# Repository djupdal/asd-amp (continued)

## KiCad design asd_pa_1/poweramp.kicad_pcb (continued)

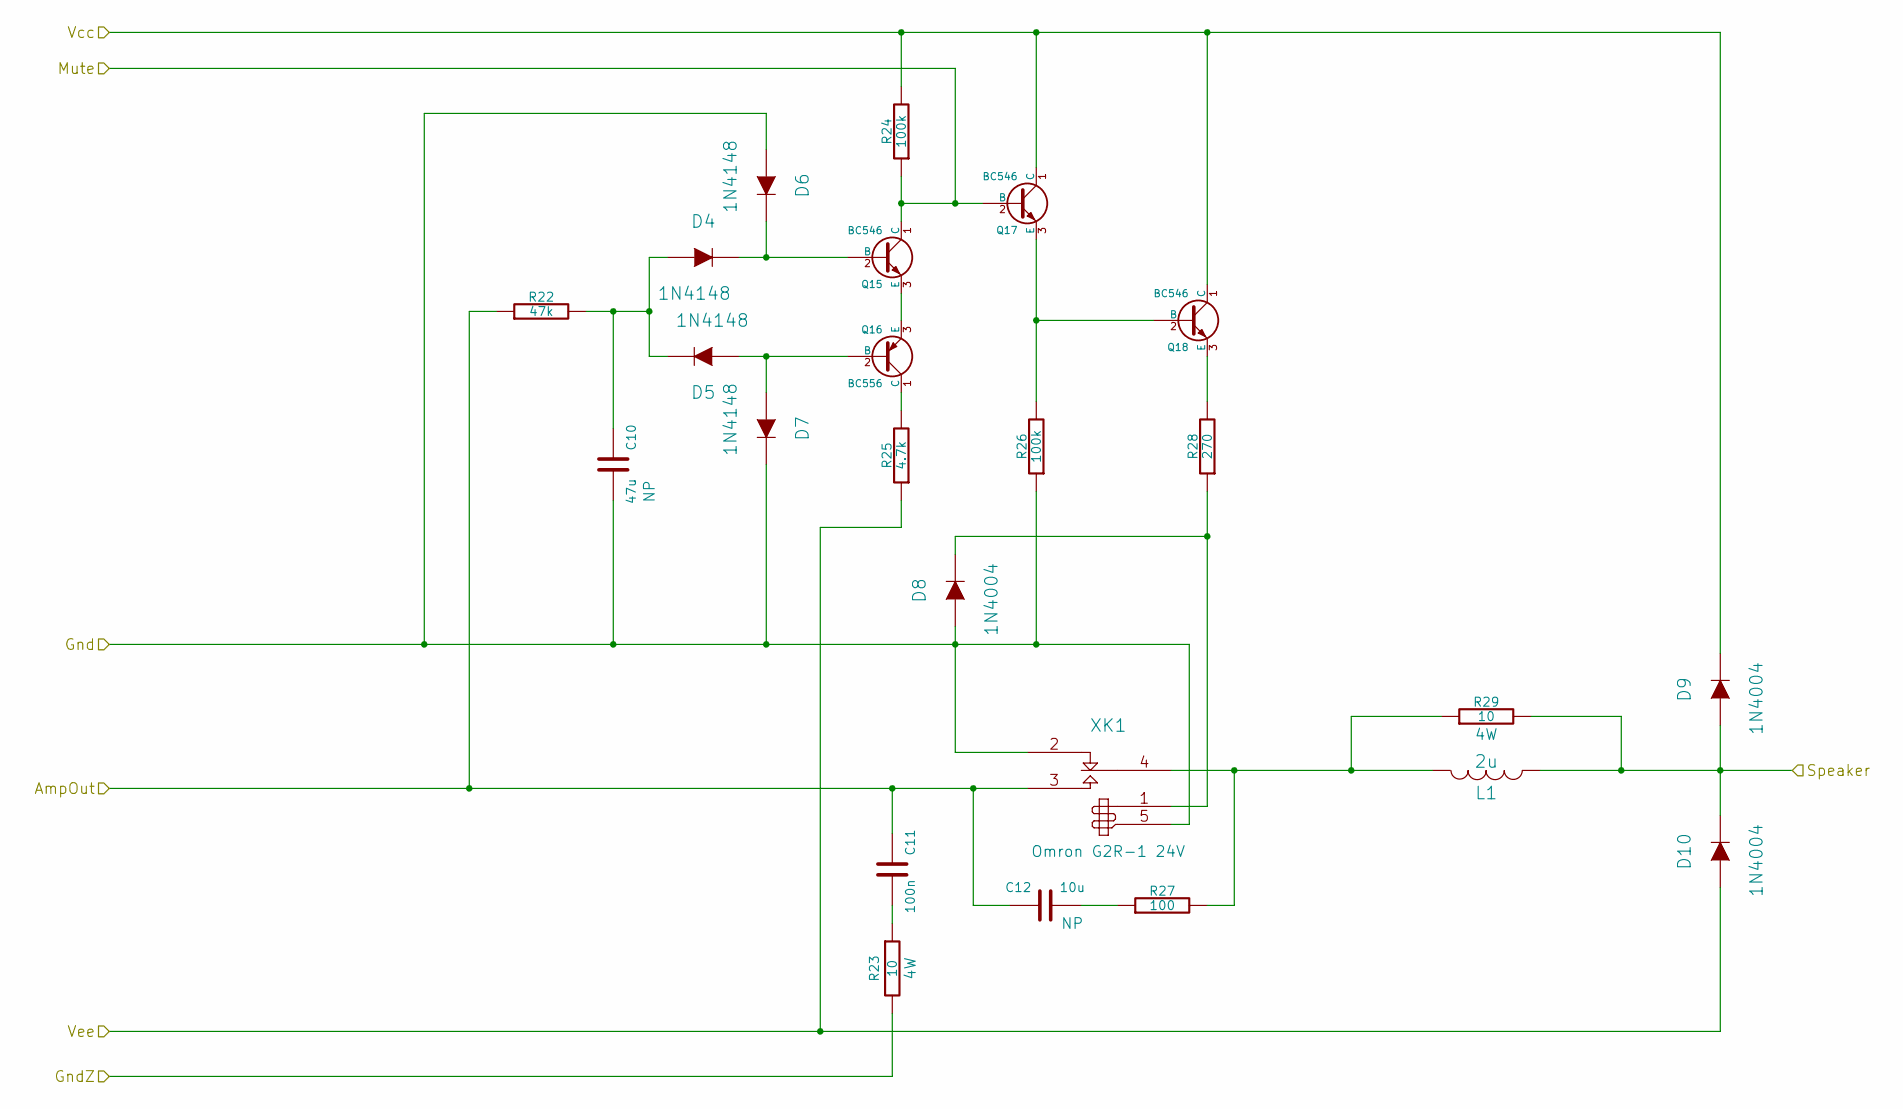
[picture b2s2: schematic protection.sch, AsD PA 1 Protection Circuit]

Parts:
C10: 47u; 47u_NP
C11: 100n; Capacitor7x2.5RM5
C12: 10u; 47u_NP
D4, D5, D6, D7: 1N4148; Diode_DO-35_SOD27_Horizontal_RM10
D8, D9, D10: 1N4004; Diode_DO-41_SOD81_Horizontal_RM10
L1: 2u; Inductor_AirCore_2uH
Q15, Q17, Q18: BC546; TO-92-Free-inline-narrow-oval
Q16: BC556; TO-92-Free-inline-narrow-oval
R22: 47k; Resistor_Horizontal_RM10mm
R23, R29: 10; Resistor_Horizontal_RM15mm
R24, R26: 100k; Resistor_Horizontal_RM10mm
R25: 4.7k; Resistor_Horizontal_RM10mm
R27: 100; Resistor_Horizontal_RM10mm
R28: 270; Resistor_Horizontal_RM10mm
XK1: RELAY_SPDT; Omron_G2R_SPDT

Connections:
/Protection/AmpOut: C11.1, C12.1, R22.1, XK1.3 (T1); also elsewhere on the board
/Protection/Gnd: C10.2, D6.1 (A), D7.2 (K), D8.1 (A), R26.1, XK1.2 (R1), XK1.5; also elsewhere on the board
/Protection/GndZ: R23.2; also elsewhere on the board
/Protection/Mute: Q15.1 (C), Q17.2 (B), R24.1; also elsewhere on the board
/Protection/Speaker: D9.1 (A), D10.2 (K), L1.2, R29.2; also elsewhere on the board
unnamed: C10.1, D4.1 (A), D5.2 (K), R22.2
unnamed: C11.2, R23.1
unnamed: C12.2, R27.1
unnamed: D4.2 (K), D6.2 (K), Q15.2 (B)
unnamed: D5.1 (A), D7.1 (A), Q16.2 (B)
unnamed: D8.2 (K), R28.1, XK1.1
unnamed: L1.1, R27.2, R29.1, XK1.4 (C1)
unnamed: Q15.3 (E), Q16.3 (E)
unnamed: Q16.1 (C), R25.2
unnamed: Q17.3 (E), Q18.2 (B), R26.2
unnamed: Q18.3 (E), R28.2
VCC: D9.2 (K), Q17.1 (C), Q18.1 (C), R24.2; also elsewhere on the board
VEE: D10.1 (A), R25.1; also elsewhere on the board

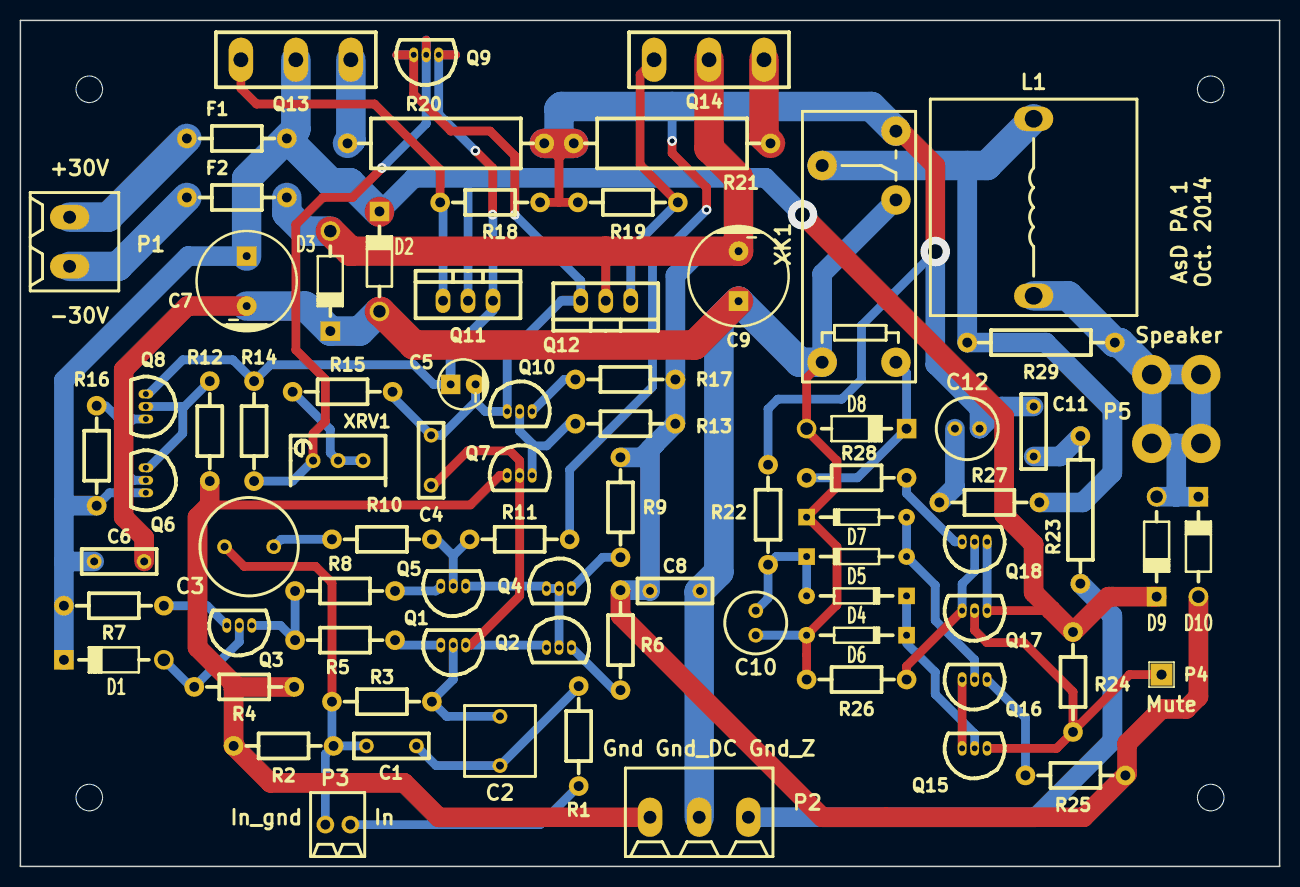
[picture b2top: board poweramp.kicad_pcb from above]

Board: 2 copper layers, 128.0 x 86.0 mm, 83 parts (0 on the bottom side), 48 nets.

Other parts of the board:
MH: MountingHole_2-7mm_RevA_Date21Jun2010; MountingHole_2-7mm
MH#2, MH#3, MH#4: MountingHole_2-7mm_RevA_Date21Jun2010; MountingHole_2-7mm

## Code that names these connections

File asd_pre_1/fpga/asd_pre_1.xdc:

###############################################################################
# Timing constraints
###############################################################################

create_clock -period 20.000 -name mcu_clk [get_ports MCU_OSC]
create_clock -period 88.000 -name audio_clk [get_ports AUDIO_OSC]
create_clock -period 41.000 -name spi_clk [get_ports SCLK]
create_clock -period 40.000 -name spdif_sck [get_ports SCKI1]
create_clock -period 162.000 -name spdif_bck [get_ports BCKI1]
create_clock -period 162.000 -name adc_bck [get_ports BCKI2]

###############################################################################
# Clock groups
###############################################################################

set_clock_groups -asynchronous -group mcu_clk -group audio_clk -group spi_clk -group spdif_sck -group spdif_bck -group adc_bck

###############################################################################
# IO standard
###############################################################################

set_property IOSTANDARD LVCMOS33 [get_ports *]
set_property CFGBVS VCCO [current_design]
set_property CONFIG_VOLTAGE 3.3 [current_design]

###############################################################################
# Location constraints
###############################################################################

# MCU SPI
#set_property PACKAGE_PIN K13 [get_ports INT]
#set_property PACKAGE_PIN P16 [get_ports nSS]
set_property PACKAGE_PIN P16 [get_ports INT]
set_property PACKAGE_PIN K13 [get_ports nSS]
set_property PACKAGE_PIN L14 [get_ports MOSI]
set_property PACKAGE_PIN M16 [get_ports MISO]
set_property PACKAGE_PIN N13 [get_ports SCLK]

# Oscillators
set_property PACKAGE_PIN N14 [get_ports MCU_OSC]
set_property PACKAGE_PIN N11 [get_ports AUDIO_OSC]

# SPDIF routing
set_property PACKAGE_PIN T8 [get_ports SPDIF]
set_property PACKAGE_PIN T9 [get_ports SPDIF_COAX]
set_property PACKAGE_PIN T10 [get_ports SPDIF_TOSLINK]

# SPDIF input
set_property PACKAGE_PIN T7 [get_ports EMPH]
set_property PACKAGE_PIN H13 [get_ports ERROR]
set_property PACKAGE_PIN D13 [get_ports SCKI1]
set_property PACKAGE_PIN H11 [get_ports LRCKI1]
set_property PACKAGE_PIN E11 [get_ports BCKI1]
set_property PACKAGE_PIN H12 [get_ports DIN1]

# ADC input
set_property PACKAGE_PIN B16 [get_ports nOVFL]
set_property PACKAGE_PIN A14 [get_ports SCKO2]
set_property PACKAGE_PIN A13 [get_ports LRCKI2]
set_property PACKAGE_PIN E12 [get_ports BCKI2]
set_property PACKAGE_PIN C14 [get_ports DIN2]

# DAC output
set_property PACKAGE_PIN B11 [get_ports SCKO]
set_property PACKAGE_PIN A10 [get_ports LRCKO]
set_property PACKAGE_PIN A9 [get_ports BCKO]
set_property PACKAGE_PIN A8 [get_ports DOUT]

###############################################################################
# Bitfile constraints
###############################################################################

set_property BITSTREAM.CONFIG.SPI_BUSWIDTH 4 [current_design]
set_property CONFIG_MODE SPIx4 [current_design]

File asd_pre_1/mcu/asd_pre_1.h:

#ifndef ASD_PRE_1_H
#define ASD_PRE_1_H

#define IN_ADDR_T_DEFINED

#include <stdint.h>
#include <stdbool.h>
#include <stddef.h>

#include "efm32gg232f1024.h"

#include "config.h"

#include "em_device.h"
#include "em_cmu.h"
#include "em_gpio.h"
#include "em_i2c.h"
#include "em_system.h"
#include "em_chip.h"
 
#define LED_ON  0
#define LED_OFF 1

#define DAC_ADDRESS 0x98

//

#define LED0_BIT 3
#define LED0_PORT gpioPortF
#define LED1_BIT 4
#define LED1_PORT gpioPortF
#define LED2_BIT GPIO_1_BIT
#define LED2_PORT GPIO_1_PORT
 
#define PROGRAM_B_BIT 4
#define PROGRAM_B_PORT gpioPortA
#define DONE_BIT 5
#define DONE_PORT gpioPortA
#define FPGA_USART USART2
#define FPGA_USART_CLK cmuClock_USART2
#define FPGA_USART_LOC USART_ROUTE_LOCATION_LOC0
#define FPGA_TX_BIT 2
#define FPGA_TX_PORT gpioPortC
#define FPGA_RX_BIT 3
#define FPGA_RX_PORT gpioPortC
#define FPGA_CLK_BIT 4
#define FPGA_CLK_PORT gpioPortC
//#define FPGA_CS_BIT 5
//#define FPGA_CS_PORT gpioPortC
//#define INT_FPGA_BIT 3
//#define INT_FPGA_PORT gpioPortA
#define FPGA_CS_BIT 3
#define FPGA_CS_PORT gpioPortA
#define INT_FPGA_BIT 5
#define INT_FPGA_PORT gpioPortC

#define nRST_SPDIF_BIT 8
#define nRST_SPDIF_PORT gpioPortB

#define nRST_DAC_BIT 15
#define nRST_DAC_PORT gpioPortE

#define nRST_ADC_BIT 14
#define nRST_ADC_PORT gpioPortE
#define nHPF_BIT 13
#define nHPF_PORT gpioPortE
#define M0_BIT 12
#define M0_PORT gpioPortE

#define WRITE_PROTECT_BIT 6
#define WRITE_PROTECT_PORT gpioPortC
#define CARD_DETECT_BIT 7
#define CARD_DETECT_PORT gpioPortC
#define SD_USART USART0
#define SD_USART_CLK cmuClock_USART0
#define SD_USART_LOC USART_ROUTE_LOCATION_LOC2
#define SD_TX_BIT 11
#define SD_TX_PORT gpioPortC
#define SD_RX_BIT 10
#define SD_RX_PORT gpioPortC
#define SD_CLK_BIT 9
#define SD_CLK_PORT gpioPortC
#define SD_CS_BIT 8
#define SD_CS_PORT gpioPortC

#define MUTE_BIT 12
#define MUTE_PORT gpioPortC

#define nINT_ETH_BIT 4
#define nINT_ETH_PORT gpioPortD
#define ETH_USART USART1
#define ETH_USART_CLK cmuClock_USART1
#define ETH_USART_LOC USART_ROUTE_LOCATION_LOC1
#define ETH_TX_BIT 0
#define ETH_TX_PORT gpioPortD
#define ETH_RX_BIT 1
#define ETH_RX_PORT gpioPortD
#define ETH_CLK_BIT 2
#define ETH_CLK_PORT gpioPortD
#define ETH_CS_BIT 3
#define ETH_CS_PORT gpioPortD

#define VOL_A_BIT 14
#define VOL_A_PORT gpioPortC
#define VOL_B_BIT 15
#define VOL_B_PORT gpioPortC

#define SOURCE_BIT GPIO_0_BIT
#define SOURCE_PORT GPIO_0_PORT

#define GPIO_0_BIT 6
#define GPIO_0_PORT gpioPortD
#define GPIO_1_BIT 7
#define GPIO_1_PORT gpioPortD
#define GPIO_2_BIT 8
#define GPIO_2_PORT gpioPortD
#define GPIO_3_BIT 13
#define GPIO_3_PORT gpioPortC

#define I2C_SCL_BIT 1
#define I2C_SCL_PORT gpioPortA
#define I2C_SDA_BIT 0
#define I2C_SDA_PORT gpioPortA

///////////////////////////////////////////////////////////////////////////////

#define INT_ETH 0x10
#define INT_SOURCE 0x40
#define INT_SD 0x80
#define INT_VOL_EVEN 0x4000
#define INT_VOL_ODD 0x8000

#define FPGA_SOURCE_COAX 0
#define FPGA_SOURCE_TOSLINK 1
#define FPGA_SOURCE_ADC 2

void swoInit(void);

void fpgaInit(uint8_t source, uint8_t gain);
void fpgaSelectSource(uint8_t source);
void fpgaSetGain(uint8_t gain);

void dacInit(uint8_t startVol);

void dacMute(bool on);
void dacSetVolume(uint8_t vol);

void setLed(int led);
void clearLed(int led);

void msleep(uint32_t ms);
void usleep(uint16_t us);

void panic(const char *fmt, ...);

bool netInit(void);
void netIRQ();
void netPeriodic(void);

#define VOL_MAX 1600
#define VOL_MIN 0
#define SOURCES 3
#define MAX_GAIN 3

extern bool saveSettings;

extern int16_t volume;
extern int source;
extern int gain;
extern bool mute;
void setVol(int16_t newVolume);
void setSource(int newSource);
void setGain(int newGain);
void setMute(bool newMute);

#endif

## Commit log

2015-04-20 Bugfix
2015-05-10 Added network protocol. Support for volume and source management.
2015-05-10 Net protocol. Added (empty) android project.
2015-05-10 Net protocol
2015-05-10 First functional android app. Volume and source selection.
2015-05-10 Does not close socket immediately
2015-05-12 More net
2015-05-12 Led off when muted
2016-01-28 Muting ved bruk av kildevelger
2016-01-31 FPGA audio path framework finished. Added gain module
2016-01-31 Android app updated.
2017-04-02 Updated schematics and PCB. Removed some minor errors with the first prototype.
2021-06-08 Ikke lagre til SD-kort
2021-06-08 Missing file
